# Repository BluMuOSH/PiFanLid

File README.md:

# PiFanLid
Welcome to the Pi Fan LID (LID = Layer Incorporating Devices.) A PCB with a fan to keep your Raspberry Pi cool

It is intended to sit on top of a Raspberry Pi 4B, but will work on a 3B or 3B+ too.

An NPN transistor is included to allow PWM control of the fan speed through any of eight different GPIO pins. GPIO18 allows hardware PWM, but software PWM works well enough in this application and is available on any of the GPIO pins.

The three files: PiFanLidR1.pro, PiFanLidR1.sch, and PiFanLidR1.kicad_pcb constitute a KiCAD project. (KiCAD is an open source schematic capture and PCB layout program.) You can download KiCAD to open the project and possibly make changes, or send PiFanLidR1.kicad_pcb to https://oshpark.com/ to have a PCB made. They should charge around $25 or $30 for three boards.

Or... drop me an email. If I have any boards left over, I might send you one by USPS.

Required materials:

1. PCB
2. 5V, 30x30mm fan (available from adafruit)
3. PN2222 transistor
4. base current limiting resistor (1k works well)
5. freewheeling diode (1N4001 for example)
6. 2x20 pin header socket (available from adafruit. The extra tall version is recommended.)
7. standoffs to support the PCB. 4 is best. 2 is OK. You can get away with none if you handle carefully.

fan-ctrl.py is a python script that will control the speed of the fan depending on the temperature of the CPU.
fan-ctrl.sh is a shell script that can be used to start fan-ctrl.py at boot up. See Pi Lid Assembly and Installation.pdf for instructions.

Aerandir14 wrote an excellent description of the circuit. It can be found at
https://www.instructables.com/id/PWM-Regulated-Fan-Based-on-CPU-Temperature-for-Ras/

My python code is based loosely on his.

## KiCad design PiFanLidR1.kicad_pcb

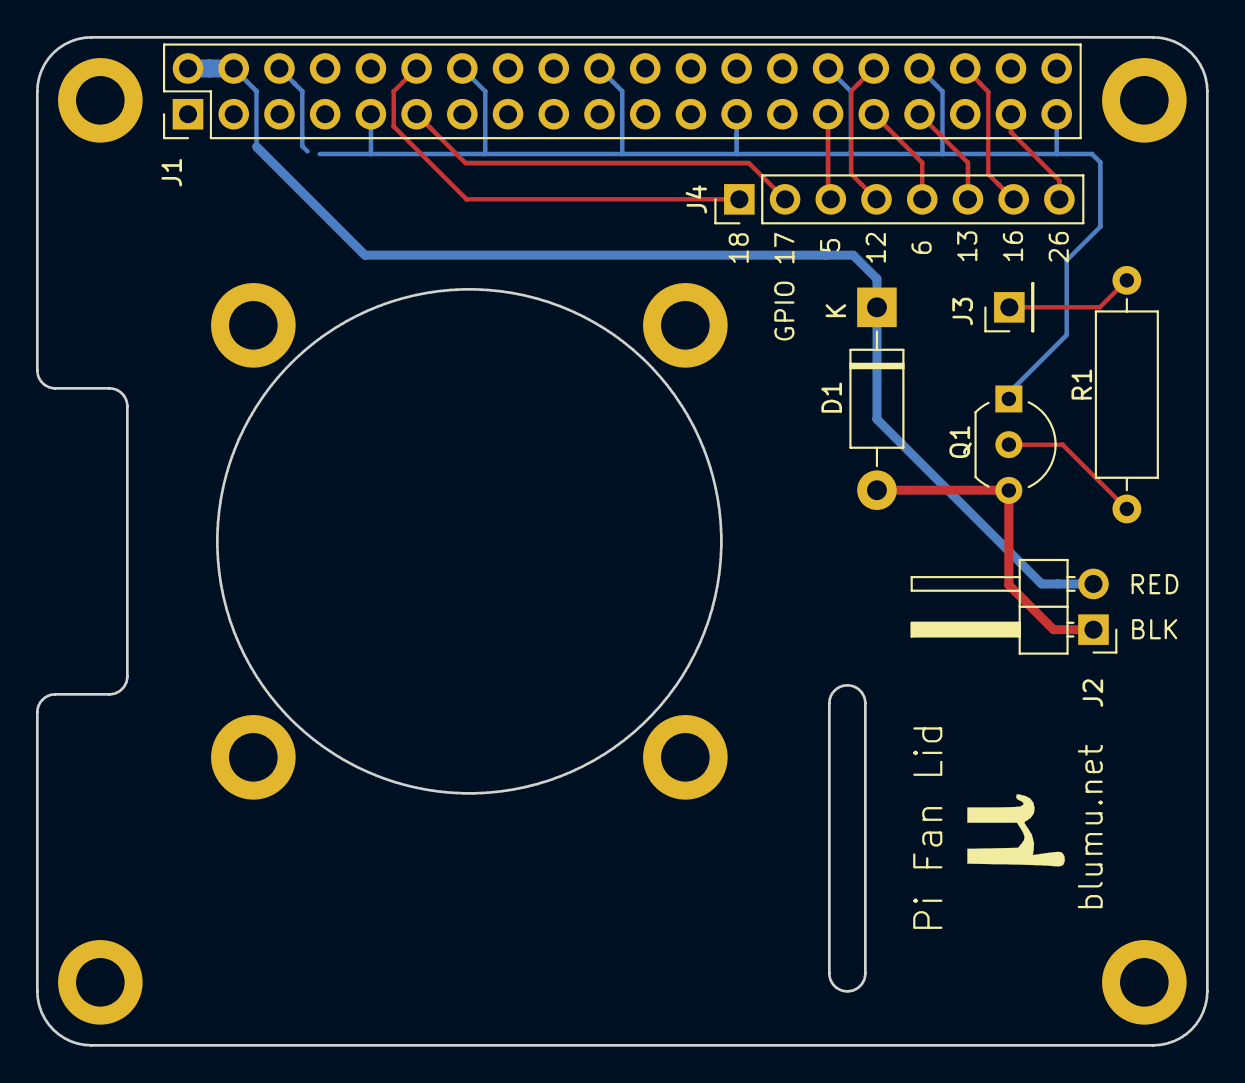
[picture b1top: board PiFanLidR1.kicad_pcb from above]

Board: 2 copper layers, 65.0 x 56.0 mm, 15 parts (0 on the bottom side), 13 nets.

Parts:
D1: 1N4001; D_DO-41_SOD81_P10.16mm_Horizontal
H1, H2, H3, H4, H5, H6, H7, H8: MountingHole; MountingHole_2.7mm_M2.5_DIN965_Pad
J1: Conn_02x20_Odd_Even; PinHeader_2x20_P2.54mm_Vertical
J2: Conn_01x02; PinHeader_1x02_P2.54mm_Horizontal
J3: Conn_01x01; PinHeader_1x01_P2.54mm_Vertical
J4: Conn_01x08; PinHeader_1x08_P2.54mm_Vertical
Q1: PN2222A; TO-92_Inline_Wide
R1: 1k; R_Axial_DIN0309_L9.0mm_D3.2mm_P12.70mm_Horizontal

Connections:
5V: D1.1, J1.2, J1.4, J2.2
/GPIO5: J1.29, J4.3
/GPIO6: J1.31, J4.5
/GPIO12: J1.32, J4.4
/GPIO13: J1.33, J4.6
/GPIO16: J1.36, J4.7
/GPIO17: J1.11, J4.2
/GPIO18: J1.12, J4.1
/GPIO26: J1.37, J4.8
/PWM: D1.2, J2.1, Q1.3
GND: J1.6, J1.9, J1.14, J1.20, J1.25, J1.30, J1.34, J1.39, Q1.1
unnamed: J3.1, R1.2
unnamed: Q1.2, R1.1

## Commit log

2019-12-12 Delete PiFanLidR1.pdf
    replaced with same file different name
